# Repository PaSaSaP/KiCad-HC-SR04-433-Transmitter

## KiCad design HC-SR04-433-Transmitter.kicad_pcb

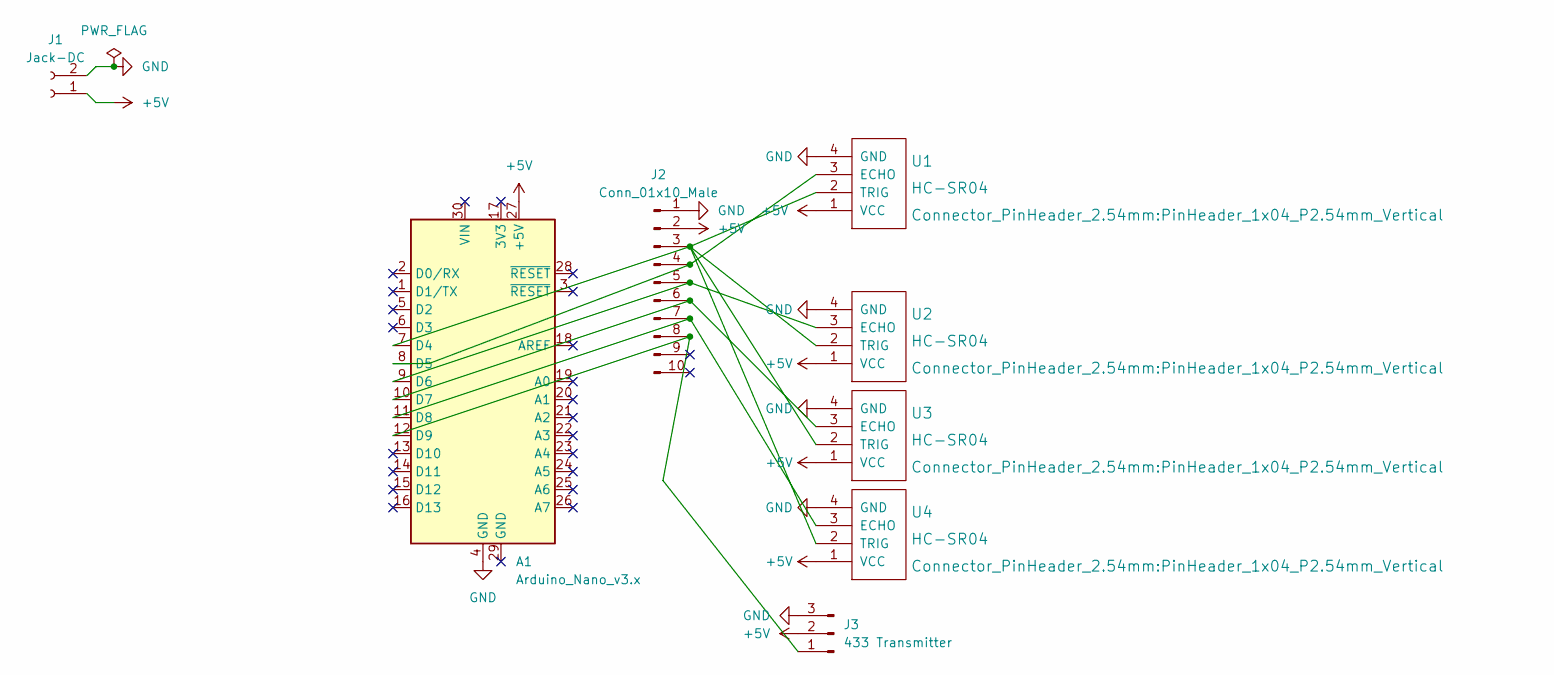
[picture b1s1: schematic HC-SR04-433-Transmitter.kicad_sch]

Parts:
A1: Arduino_Nano_v3.x; Arduino_Nano
J1: Jack-DC; PinSocket_1x02_P2.54mm_Vertical
J2: Conn_01x10_Male; PinHeader_1x10_P2.54mm_Vertical
J3: 433 Transmitter; PinHeader_1x03_P2.54mm_Vertical
U1, U2, U3, U4: HC-SR04; PinHeader_1x04_P2.54mm_Vertical

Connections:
+5V: A1.27 (+5V), J1.1, J2.2, J3.2, U1.1 (VCC), U2.1 (VCC), U3.1 (VCC), U4.1 (VCC)
GND: A1.4 (GND), J1.2, J2.1, J3.3, U1.4 (GND), U2.4 (GND), U3.4 (GND), U4.4 (GND)
unnamed: A1.7 (D4), J2.3, U1.2 (TRIG), U2.2 (TRIG), U3.2 (TRIG), U4.2 (TRIG)
unnamed: A1.8 (D5), J2.4, U1.3 (ECHO)
unnamed: A1.9 (D6), J2.5, U2.3 (ECHO)
unnamed: A1.10 (D7), J2.6, U3.3 (ECHO)
unnamed: A1.11 (D8), J2.7, U4.3 (ECHO)
unnamed: A1.12 (D9), J2.8, J3.1

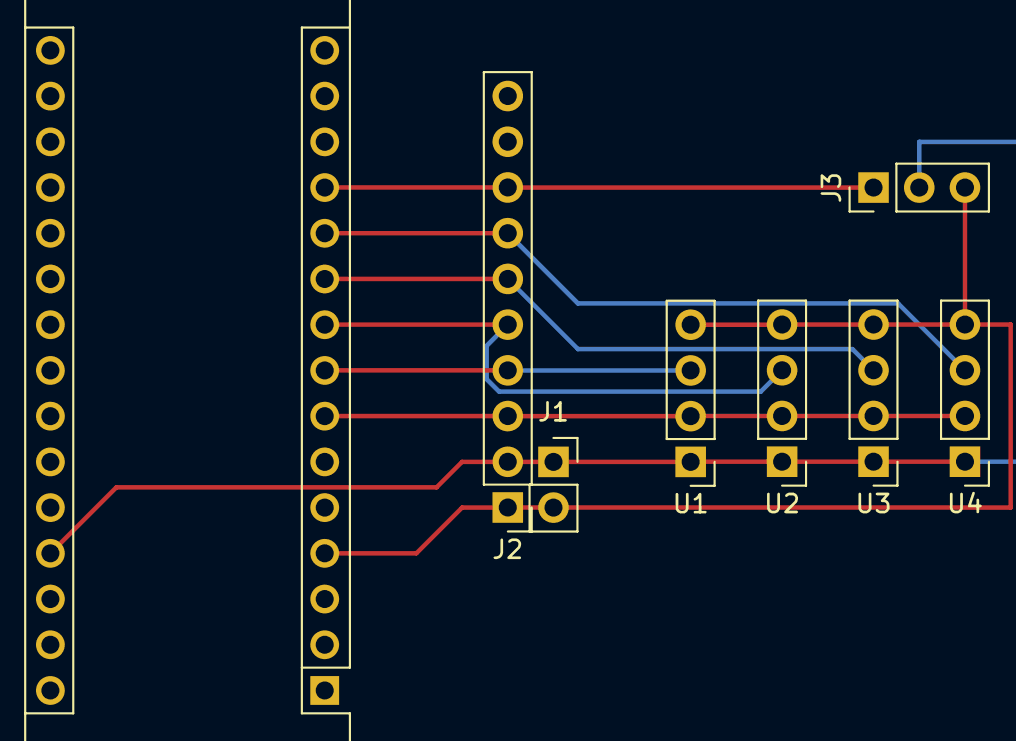
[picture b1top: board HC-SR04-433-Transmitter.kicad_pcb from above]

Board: 2 copper layers, 8 parts (0 on the bottom side), 8 nets.
